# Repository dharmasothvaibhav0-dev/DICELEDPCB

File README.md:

# DICELEDPCB
Using IC's NE555, and CD4017, to create a random rolling generator for a dice (I also added a few designs to be part of the roll)
KiCanvas Demo Link! [https://kicanvas.org/?repo=https%3A%2F%2Fgithub.com%2Fdharmasothvaibhav0-dev%2FDICELEDPCB%2Ftree%2Fmain%2FKiCad%2520Source%2520files](https://kicanvas.org/?repo=https%3A%2F%2Fgithub.com%2Fdharmasothvaibhav0-dev%2FDICELEDPCB%2Ftree%2Fmain%2FKiCad%2520Source%2520files)

_______________________________________________________________________________________________________

# The Schematic

The actual schematic probably took the longest because the design and wiring. I used 2 Capacitors of 1uF and 0.01uF, 14 LEDS, 6 Transistors, 26 resistors which consisted of values of 10k and 220, 1 push button, and 2 IC's: A NE555, and a CD4017.

Essentially what happens in the circuit is, the NE555 in its astable option, send currents to the CD4017 which acts as a clock, and whenever it recieves the current it cycles through each output. When you push the button it cycles through, and when you let go of the button it gives you an output of a number 1-6 OR one of the 2 special designs i put in.

___________________________________________________________________________________________________________________

# PCB Designs

Front :

Back:

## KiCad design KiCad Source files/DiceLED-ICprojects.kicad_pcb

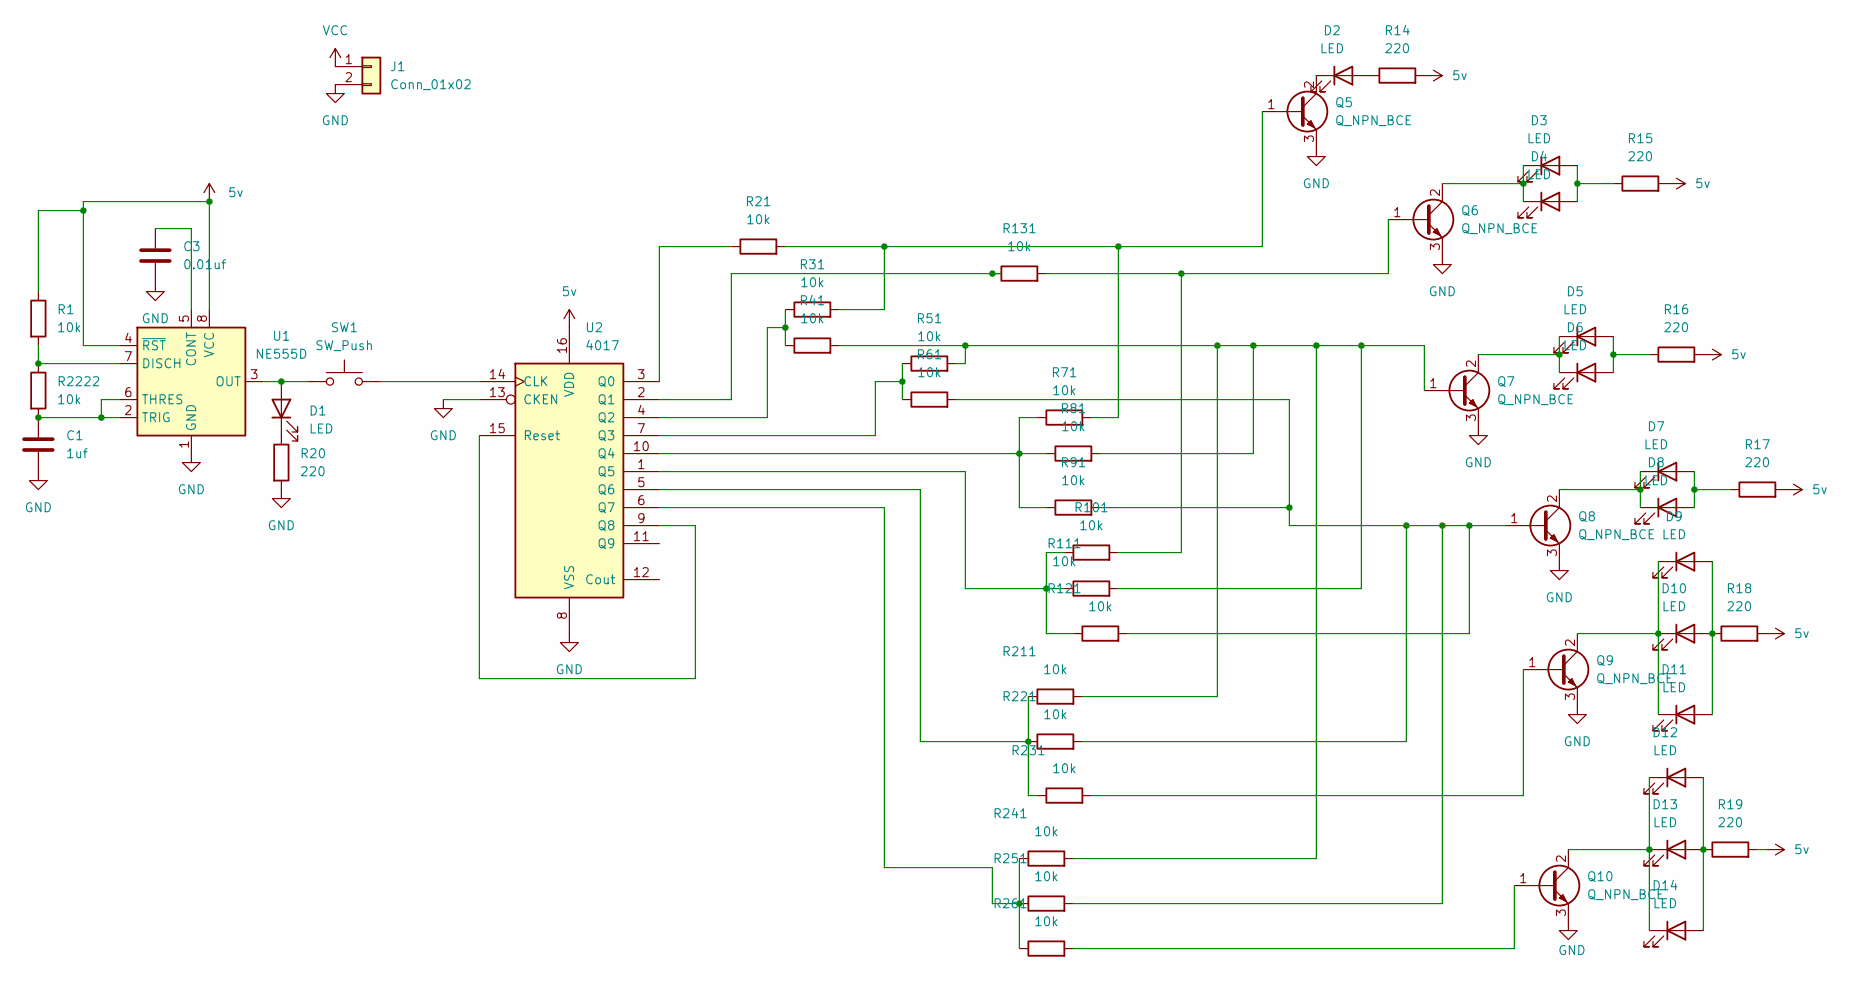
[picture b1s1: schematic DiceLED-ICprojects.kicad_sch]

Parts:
C1: 1uf; C_Disc_D5.0mm_W2.5mm_P5.00mm
C3: 0.01uf; C_Disc_D5.0mm_W2.5mm_P5.00mm
D1, D2, D3, D4, D5, D6, D7, D8, D9, D10, D11, D12, D13, D14: LED; LED_D5.0mm
J1: Conn_01x02; PinHeader_1x02_P2.54mm_Vertical
Q5, Q6, Q7, Q8, Q9, Q10: Q_NPN_BCE; TO-92L_Inline_Wide
R1, R21, R31, R41, R51, R61, R71, R81, R91, R101, R111, R121, R131, R211, R221, R231, R241, R251, R261, R2222: 10k; R_Axial_DIN0204_L3.6mm_D1.6mm_P7.62mm_Horizontal
R14, R15, R16, R17, R18, R19, R20: 220; R_Axial_DIN0204_L3.6mm_D1.6mm_P7.62mm_Horizontal
SW1: SW_Push; SW_PUSH_6mm
U1: NE555D; SOIC-8_3.9x4.9mm_P1.27mm
U2: 4017; DIP-16_W7.62mm

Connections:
5v: R1.1, R14.2, R15.2, R16.2, R17.2, R18.2, R19.2, U1.4 (~RST), U1.8 (VCC), U2.16 (VDD)
GND: C1.2, C3.2, J1.2, Q5.3 (E), Q6.3 (E), Q7.3 (E), Q8.3 (E), Q9.3 (E), Q10.3 (E), R20.2, U1.1 (GND), U2.8 (VSS), U2.13 (CKEN)
unnamed: D1.2 (A), SW1.1, U1.3 (OUT)
unnamed: D1.1 (K), R20.1
unnamed: D2.2 (A), R14.1
unnamed: D2.1 (K), Q5.2 (C)
unnamed: D3.2 (A), D4.2 (A), R15.1
unnamed: D3.1 (K), D4.1 (K), Q6.2 (C)
unnamed: D5.2 (A), D6.2 (A), R16.1
unnamed: D5.1 (K), D6.1 (K), Q7.2 (C)
unnamed: D7.2 (A), D8.2 (A), R17.1
unnamed: D7.1 (K), D8.1 (K), Q8.2 (C)
unnamed: D9.2 (A), D10.2 (A), D11.2 (A), R18.1
unnamed: D9.1 (K), D10.1 (K), D11.1 (K), Q9.2 (C)
unnamed: D12.2 (A), D13.2 (A), D14.2 (A), R19.1
unnamed: D12.1 (K), D13.1 (K), D14.1 (K), Q10.2 (C)
unnamed: Q5.1 (B), R21.2, R31.2, R71.2
unnamed: Q6.1 (B), R101.2, R131.2
unnamed: Q7.1 (B), R41.2, R51.2, R81.2, R111.2, R211.2, R241.2
unnamed: Q8.1 (B), R61.2, R91.2, R121.2, R221.2, R251.2
unnamed: Q9.1 (B), R231.2
unnamed: Q10.1 (B), R261.2
unnamed: C3.1, U1.5 (CONT)
unnamed: R1.2, R2222.1, U1.7 (DISCH)
unnamed: C1.1, R2222.2, U1.2 (TRIG), U1.6 (THRES)
unnamed: SW1.2, U2.14 (CLK)
unnamed: R21.1, U2.3 (Q0)
unnamed: R131.1, U2.2 (Q1)
unnamed: R31.1, R41.1, U2.4 (Q2)
unnamed: R51.1, R61.1, U2.7 (Q3)
unnamed: R71.1, R81.1, R91.1, U2.10 (Q4)
unnamed: R101.1, R111.1, R121.1, U2.1 (Q5)
unnamed: R211.1, R221.1, R231.1, U2.5 (Q6)
unnamed: R241.1, R251.1, R261.1, U2.6 (Q7)
unnamed: U2.9 (Q8), U2.15 (Reset)
VCC: J1.1

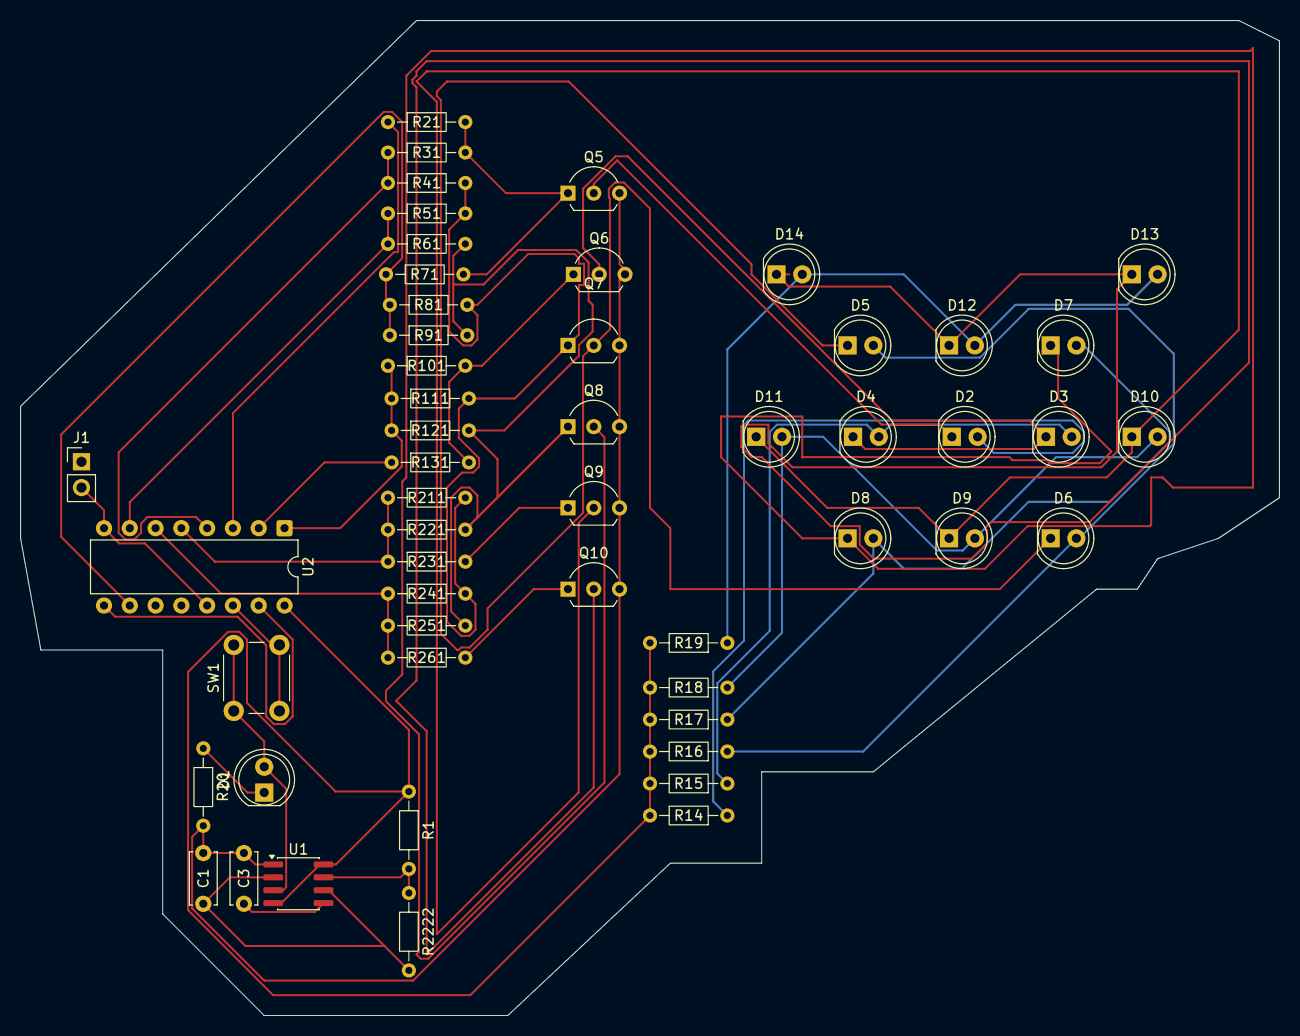
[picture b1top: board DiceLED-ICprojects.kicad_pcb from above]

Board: 2 copper layers, 124.0 x 98.0 mm, 53 parts (0 on the bottom side), 35 nets.

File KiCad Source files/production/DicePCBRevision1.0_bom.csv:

Designator,Footprint,Quantity,Value,LCSC Part #
C1,C_Disc_D5.0mm_W2.5mm_P5.00mm,1,1uf,
C3,C_Disc_D5.0mm_W2.5mm_P5.00mm,1,0.01uf,
"D1, D10, D11, D12, D13, D14, D2, D3, D4, D5, D6, D7, D8, D9",LED_D5.0mm,14,LED,
"Q10, Q5, Q6, Q7, Q8, Q9",TO-92L_Inline_Wide,6,Q_NPN_BCE,
"R1, R101, R111, R121, R131, R21, R211, R221, R2222, R231, R241, R251, R261, R31, R41, R51, R61, R71, R81, R91",R_Axial_DIN0204_L3.6mm_D1.6mm_P7.62mm_Horizontal,20,10k,
"R14, R15, R16, R17, R18, R19, R20",R_Axial_DIN0204_L3.6mm_D1.6mm_P7.62mm_Horizontal,7,220,
SW1,SW_PUSH_6mm,1,SW_Push,
U1,SOIC-8_3.9x4.9mm_P1.27mm,1,NE555D,
U2,DIP-16_W7.62mm,1,4017,
